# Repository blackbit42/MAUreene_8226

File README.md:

> [!WARNING]
> The current revision of the board is not functional. Build only if you want to work on fixing it.

# Token Ring MAU 'MAUreen'

MAUreene 8226 is a Token Ring (IEEE 802.5) Media Access Unit (MAU) that is inspired by the IBM 8226. For the most part, it is a reproduction of the IBM 8226, reduced to 2 'lobes', which is Token Ring lingo for what is known as a port in the context of other network technologies.

## Motivation

Token Ring is an interesting LAN technology. NICs are all over common auction sites and can be had cheaply, though MAUs are hard to come by. The intent of this project is to enable inclined people to play with Token Ring more easily.

## Clarification regarding 'crossover' cables

In an ethernet network you can nowadays connect two arbitrary devices with each other back to back without thinking about it, due to to the power of Auto MDI-X. Earlier you could use so-called 'crossover' cables. Unfortunately Token Ring doesn't support such a mode of interconnection, as a NIC goes through a mildly elaborated attachment process with a MAU. A mode where two hosts talk directly to each other doesn't exist, see [this](https://www.tavi.co.uk/ps2pages/ohland/8228.html#DirectCable).

## BOM analysis and mapping

| Original 8226 | Lobe 1 | Lobe 2  | Package      | Type                      | Measured value[^1] | Marking           | Remarks                             |
| ---           | ---    | ---     | ---          | ---                       | ---                | ---               | ---                                 |
| R2            | R1     | R21     | 0805         |                           | 4.8k               | 4871              |                                     |
| R10           | R2     | R22     | 0603         |                           | -None-             | -None-            | Opto-coupler biasing, not populated |
| R34           | R3     | R23     | 0603         |                           | 0.3                | 000               | RJ45 termination                    |
| R35           | R4     | R24     | 0603         |                           | 0.3                | 000               | RJ45 termination                    |
| R44           | R5     | R25     | 0603         |                           | 100                | 101               |                                     |
| R52           | R6     | R26     | 0603         |                           | 100                | 101               |                                     |
| R60           | R7     | R27     | 0603         |                           |                    | 104               |                                     |
| R68           | R8     | R28     | 0603         |                           | 10k                | 103               |                                     |
| R76           | R9     | R29     | 0603         |                           | 2k                 | 202               |                                     |
| R84           | R10    | R30     | 0805         |                           | 3.7k               | 3741              |                                     |
| R92           | R11    | R31     | 0603         |                           | 4.7k               | 472               | LED series resistor                 |
| R96           | R12    | R32     | 0603         |                           | 0.3                | 000               | RJ45 termination                    |
| R97           | R13    | R33     | 0603         |                           | 0.3                | 000               | RJ45 termination                    |
| C4            | C1     | C21     | 1812         | Ceramic                   | 330n               | -None-            |                                     |
| C12           | C2     | C22     | 1812         | Ceramic                   | 330n               | -None-            |                                     |
| C20           | C3     | C23     | EIA 7343-31  | Tantalum                  | 22u                | 22-20 LD (2)      |                                     |
| C34           | C4     | C24     | 0805         | Ceramic                   | 120n               | -None-            |                                     |
| C41           | C5     | C25     | 0805         | Ceramic                   | 120n               | -None-            |                                     |
| Q13           | Q1     | Q21     | SOT23        | BJT NPN                   |                    | 1P                |                                     |
| Q14           | Q2     | Q22     | SOT23        | BJT NPN                   |                    | 1P                |                                     |
| CR7           | D1     | D21     | SOT23        |                           | 0.6                | A66 (?)           | Flyback diode for coil in K2        |
| K2[^2]        | K1     | K21     | Non-standard | 4PDT                      |                    | P&B T84S17D214-12 |                                     |
| T2            | T1     | T21     | Non-standard | Special Token Ring        |                    | Valor PT4043      |                                     |
| DS2           | -None- | -None-  | Non-standard |                           |                    | -None-            | LEDs of J1A and J1B are used        |
| L2            | -None- | -None-  | -None-       | -None-                    |                    | -None-            | Unpopulated                         |
| U2            | U1     | U21     | DIP-6        | Opto-Coupler              |                    | QTC H11A1         |                                     | 
| -None-        | J1A    | J1B     | Non-standard | RJ45 jack                 |                    |                   |                                     |

## Power supply BOM

| Part designator | Value  | Description    |
| ---             | ---    | ---            |
| J200            |        | Barrel jack    |
| J201            |        | 2x2 jumper 12V |
| J202            |        | 2x2 jumper 5V  |
| U200            |        | 5V linear reg. |
| C200            | 0.33uF |                |
| C201            | 0.1uF  |                |
| C202            | 0.1uF  |                |
| R200            | 495Ohm | 12V rail ind.  |
| R201            | 145Ohm | 5V rail ind.   |

[^1]: Capacitors have been desoldered for measurement with HP 4262A LCR meter.
[^2]: The polarity of the coil supply is reversed, both in the original and this design. Irrelevant, as the relay coils do not have series diodes.

## Diode direction
CR7 is in a 3-pin SOT23 package, containing only a single diode. It is connected in parallel with a relay coil, indicating reverse EMF protection for adjacent devices in the circuit.
Unfortunately somebody got the direction wrong, hence there is significant reverse EMF with spikes of around 200V. 
Remarkably, neither the diode itself dies from excessive forward current when the relay is on, nor the switching transistor from the voltage spikes when the relay is being switched off.
In the design of this contraption, a diode with normal flyback operation has been foreseen.

## Pictures

Photo:

Kicad:

FreeCAD:

X-ray of original PCB, courtesy of [@Manawyrm](https://github.com/Manawyrm):

## Links

<https://www.ieee802.org/5/www8025org/>

<https://ardent-tool.com/network/Understanding_Token_Ring.html>

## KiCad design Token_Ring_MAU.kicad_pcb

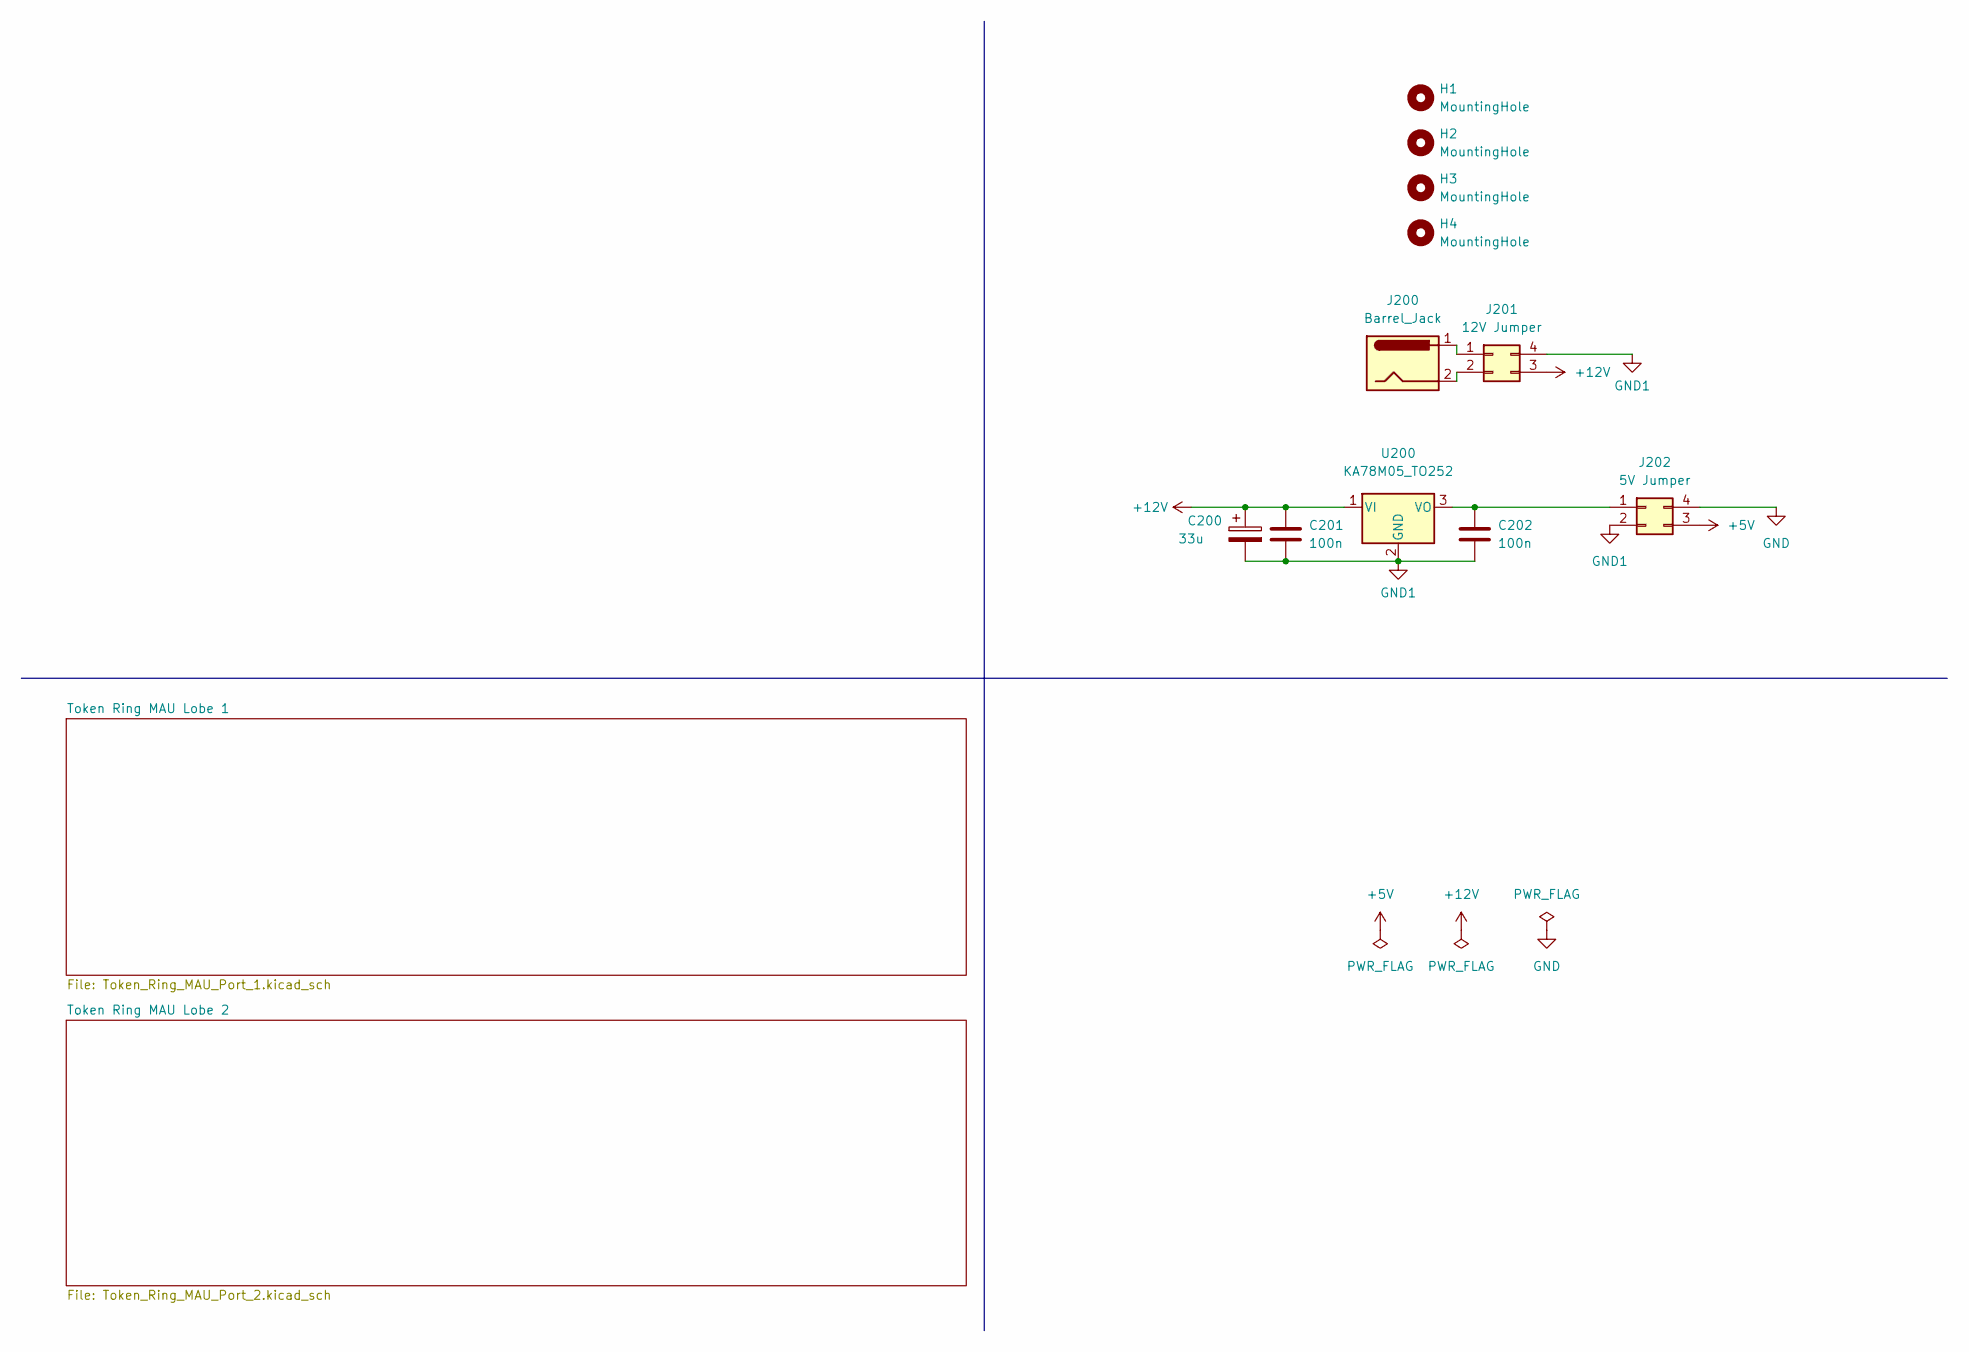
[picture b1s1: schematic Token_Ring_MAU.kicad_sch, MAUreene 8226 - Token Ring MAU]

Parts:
C200: 33u; CP_Elec_5x5.8; JLCPCB part number C128455
C201, C202: 100n; C_0805_2012Metric_Pad1.18x1.45mm_HandSolder; JLCPCB part number C85866
H1, H2, H3, H4: MountingHole; MountingHole_3.2mm_M3_DIN965_Pad; JLCPCB part number DNP
J200: Barrel_Jack; BarrelJack_CUI_PJ-063AH_Horizontal; JLCPCB part number DNP
J201: 12V Jumper; PinHeader_2x02_P2.54mm_Vertical; JLCPCB part number DNP
J202: 5V Jumper; PinHeader_2x02_P2.54mm_Vertical; JLCPCB part number DNP
U200: KA78M05_TO252; TO-252-2; JLCPCB part number DNP

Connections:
+5V: J202.3; also elsewhere on the board
+12V: C200.1, C201.1, J201.3, U200.1 (VI); also elsewhere on the board
GND: J202.4; also elsewhere on the board
GND1: C200.2, C201.2, C202.2, J201.4, J202.2, U200.2 (GND)
unnamed: C202.1, J202.1, U200.3 (VO)
unnamed: J200.1, J201.1
unnamed: J200.2, J201.2

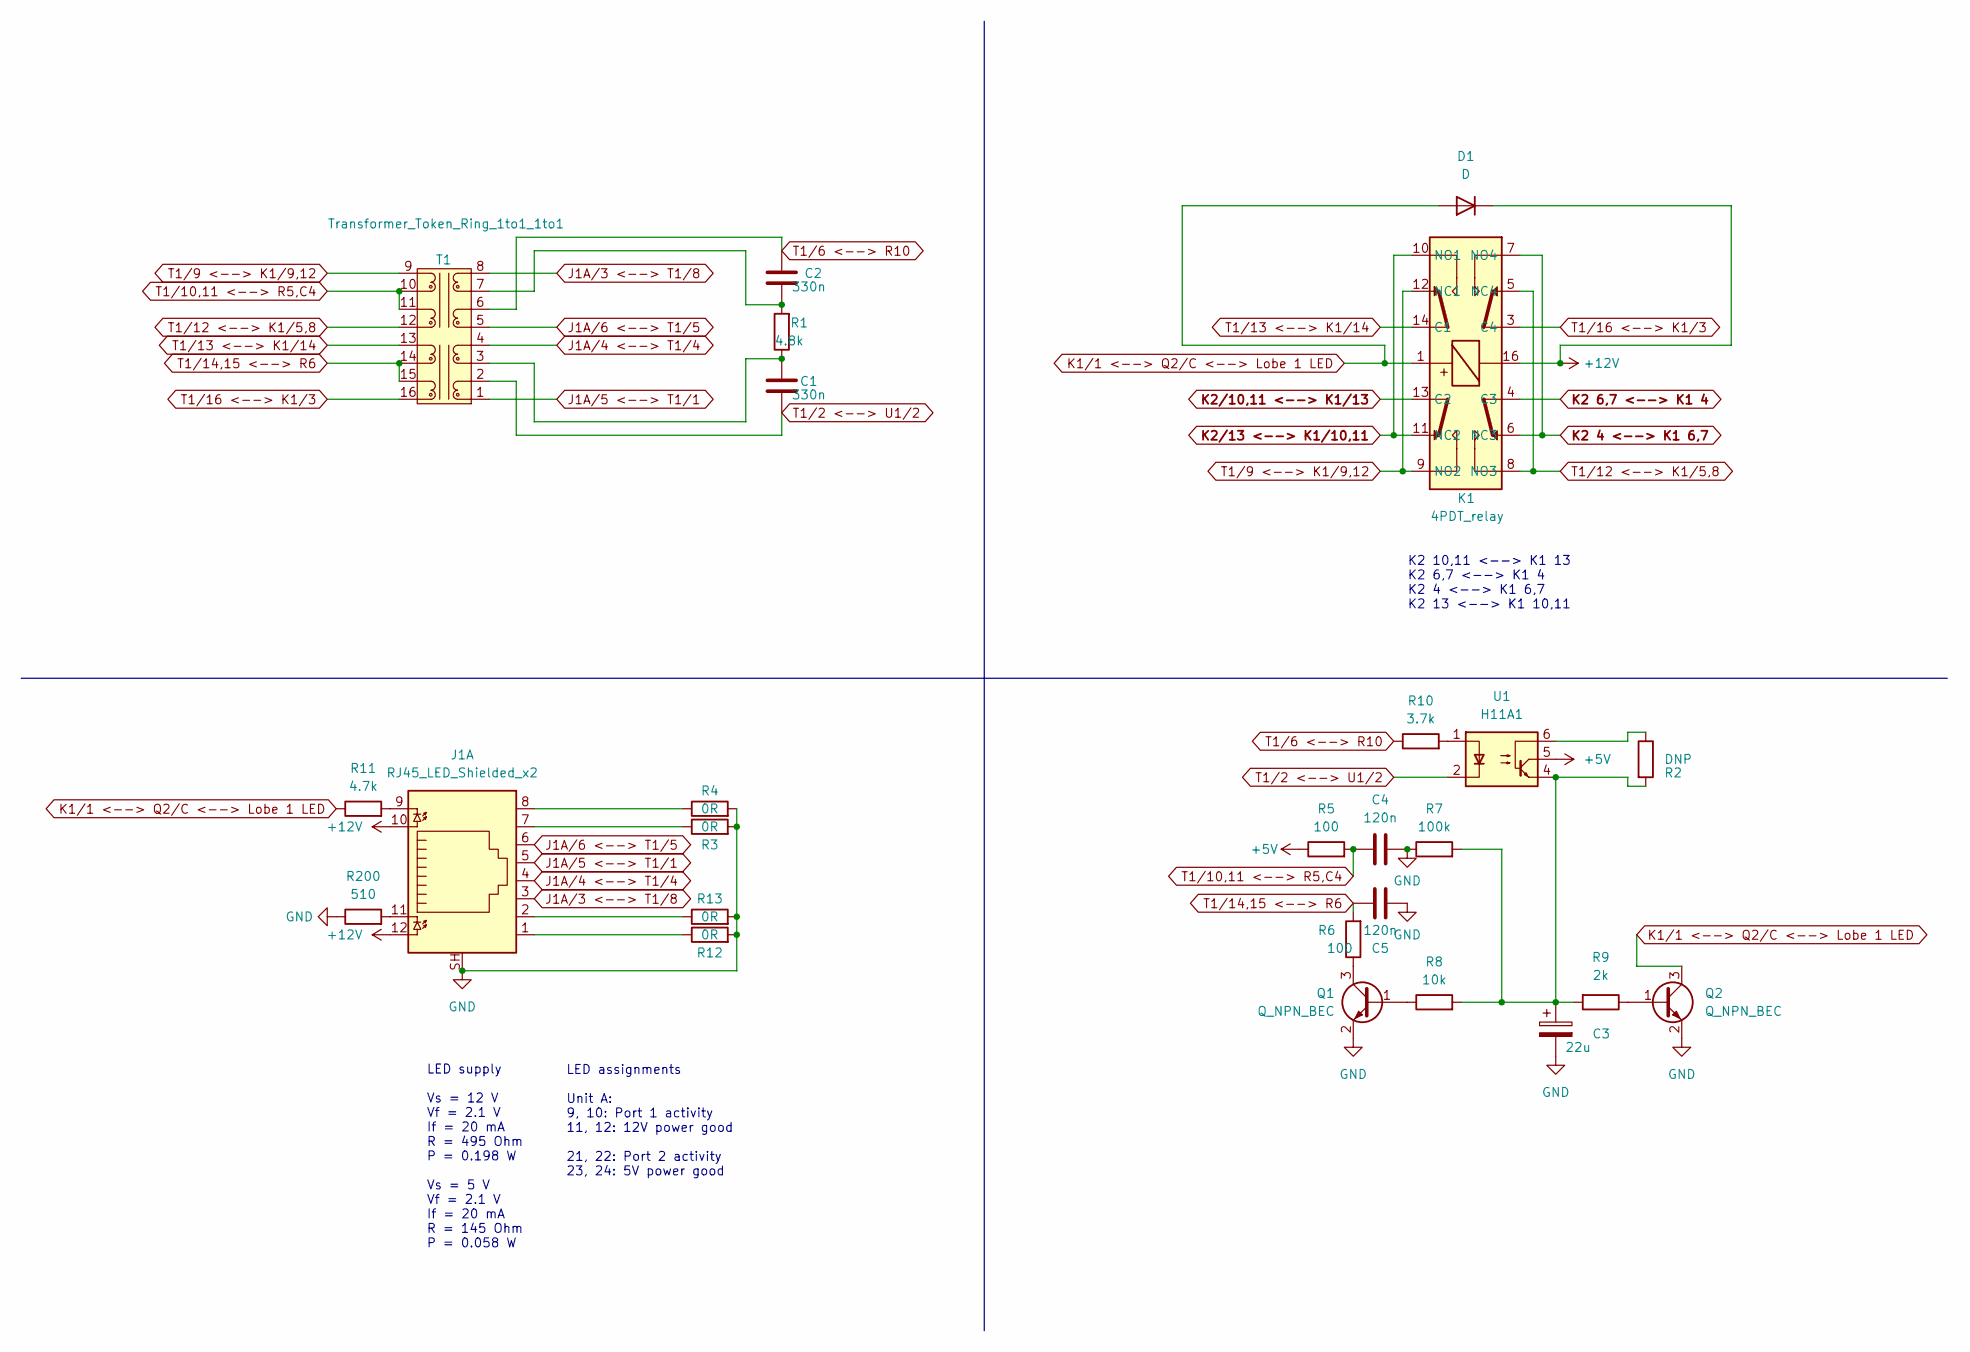
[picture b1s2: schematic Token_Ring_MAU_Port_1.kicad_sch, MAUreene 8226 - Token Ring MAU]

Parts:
C1, C2: 330n; C_1812_4532Metric_Pad1.57x3.40mm_HandSolder; JLCPCB part number C106167
C3: 22u; CP_EIA-7343-31_Kemet-D_Pad2.25x2.55mm_HandSolder; JLCPCB part number C7225
C4, C5: 120n; C_0603_1608Metric_Pad1.08x0.95mm_HandSolder; JLCPCB part number C282672
D1: D; D_SOD-123F; JLCPCB part number C108803
J1: RJ45_LED_Shielded_x2; RJ45_Amphenol_RJHSE538X-02; JLCPCB part number DNP
K1: 4PDT_relay; 4PDT_Relay; JLCPCB part number DNP
Q1, Q2: Q_NPN_BEC; SOT-23; JLCPCB part number C141788
R1: 4.8k; R_1206_3216Metric_Pad1.30x1.75mm_HandSolder; JLCPCB part number C323071
R2: DNP; R_1206_3216Metric_Pad1.30x1.75mm_HandSolder; JLCPCB part number DNP
R3, R4, R12, R13: 0R; R_0603_1608Metric_Pad0.98x0.95mm_HandSolder; JLCPCB part number C21189
R5, R6: 100; R_0603_1608Metric_Pad0.98x0.95mm_HandSolder; JLCPCB part number C445624
R7: 100k; R_0603_1608Metric_Pad0.98x0.95mm_HandSolder; JLCPCB part number C150003
R8: 10k; R_0603_1608Metric_Pad0.98x0.95mm_HandSolder; JLCPCB part number C100708
R9: 2k; R_0603_1608Metric_Pad0.98x0.95mm_HandSolder; JLCPCB part number C217936
R10: 3.7k; R_0805_2012Metric_Pad1.20x1.40mm_HandSolder; JLCPCB part number C403190
R11: 4.7k; R_0603_1608Metric_Pad0.98x0.95mm_HandSolder; JLCPCB part number C105428
R200: 510; R_0603_1608Metric_Pad0.98x0.95mm_HandSolder; JLCPCB part number C23193
T1: Transformer_Token_Ring_1to1_1to1; Pulse PE-64974; JLCPCB part number DNP
U1: H11A1; DIP-6_W7.62mm; JLCPCB part number DNP

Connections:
+5V: R5.1, U1.5; also elsewhere on the board
+12V: D1.1 (K), J1.10, J1.12, K1.16; also elsewhere on the board
GND: C3.2, C4.2, C5.2, J1.SH, Q1.2 (E), Q2.2 (E), R3.2, R4.2, R7.1, R12.2, R13.2, R200.1; also elsewhere on the board
J1A/3 <--> T1/8: J1.3, T1.8
J1A/4 <--> T1/4: J1.4, T1.4
J1A/5 <--> T1/1: J1.5, T1.1
J1A/6 <--> T1/5: J1.6, T1.5
K1/1 <--> Q2/C <--> Lobe 1 LED: D1.2 (A), K1.1, Q2.3 (C), R11.1
K2 4 <--> K1 6,7: K1.6 (NC3), K1.7 (NO4); also elsewhere on the board
K2 6,7 <--> K1 4: K1.4 (C3); also elsewhere on the board
K2/10,11 <--> K1/13: K1.13 (C2); also elsewhere on the board
K2/13 <--> K1/10,11: K1.10 (NO1), K1.11 (NC2); also elsewhere on the board
unnamed: C1.1, R1.1, T1.3
unnamed: C2.2, R1.2, T1.7
unnamed: C3.1, R2.2, R7.2, R8.2, R9.2, U1.4
unnamed: J1.1, R12.1
unnamed: J1.2, R13.1
unnamed: J1.7, R3.1
unnamed: J1.8, R4.1
unnamed: J1.9, R11.2
unnamed: J1.11, R200.2
unnamed: Q1.1 (B), R8.1
unnamed: Q1.3 (C), R6.1
unnamed: Q2.1 (B), R9.1
unnamed: R2.1, U1.6
unnamed: R10.2, U1.1
T1/2 <--> U1/2: C1.2, T1.2, U1.2
T1/6 <--> R10: C2.1, R10.1, T1.6
T1/9 <--> K1/9,12: K1.9 (NO2), K1.12 (NC1), T1.9
T1/10,11 <--> R5,C4: C4.1, R5.2, T1.10, T1.11
T1/12 <--> K1/5,8: K1.5 (NC4), K1.8 (NO3), T1.12
T1/13 <--> K1/14: K1.14 (C1), T1.13
T1/14,15 <--> R6: C5.1, R6.2, T1.14, T1.15
T1/16 <--> K1/3: K1.3 (C4), T1.16

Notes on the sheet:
K2 10,11 <--> K1 13 K2 6,7 <--> K1 4 K2 4 <--> K1 6,7 K2 13 <--> K1 10,11
LED assignments Unit A: 9, 10: Port 1 activity 11, 12: 12V power good 21, 22: Port 2 activity 23, 24: 5V power good
LED supply Vs = 12 V Vf = 2.1 V If = 20 mA R = 495 Ohm P = 0.198 W Vs = 5 V Vf = 2.1 V If = 20 mA R = 145 Ohm P = 0.058 W

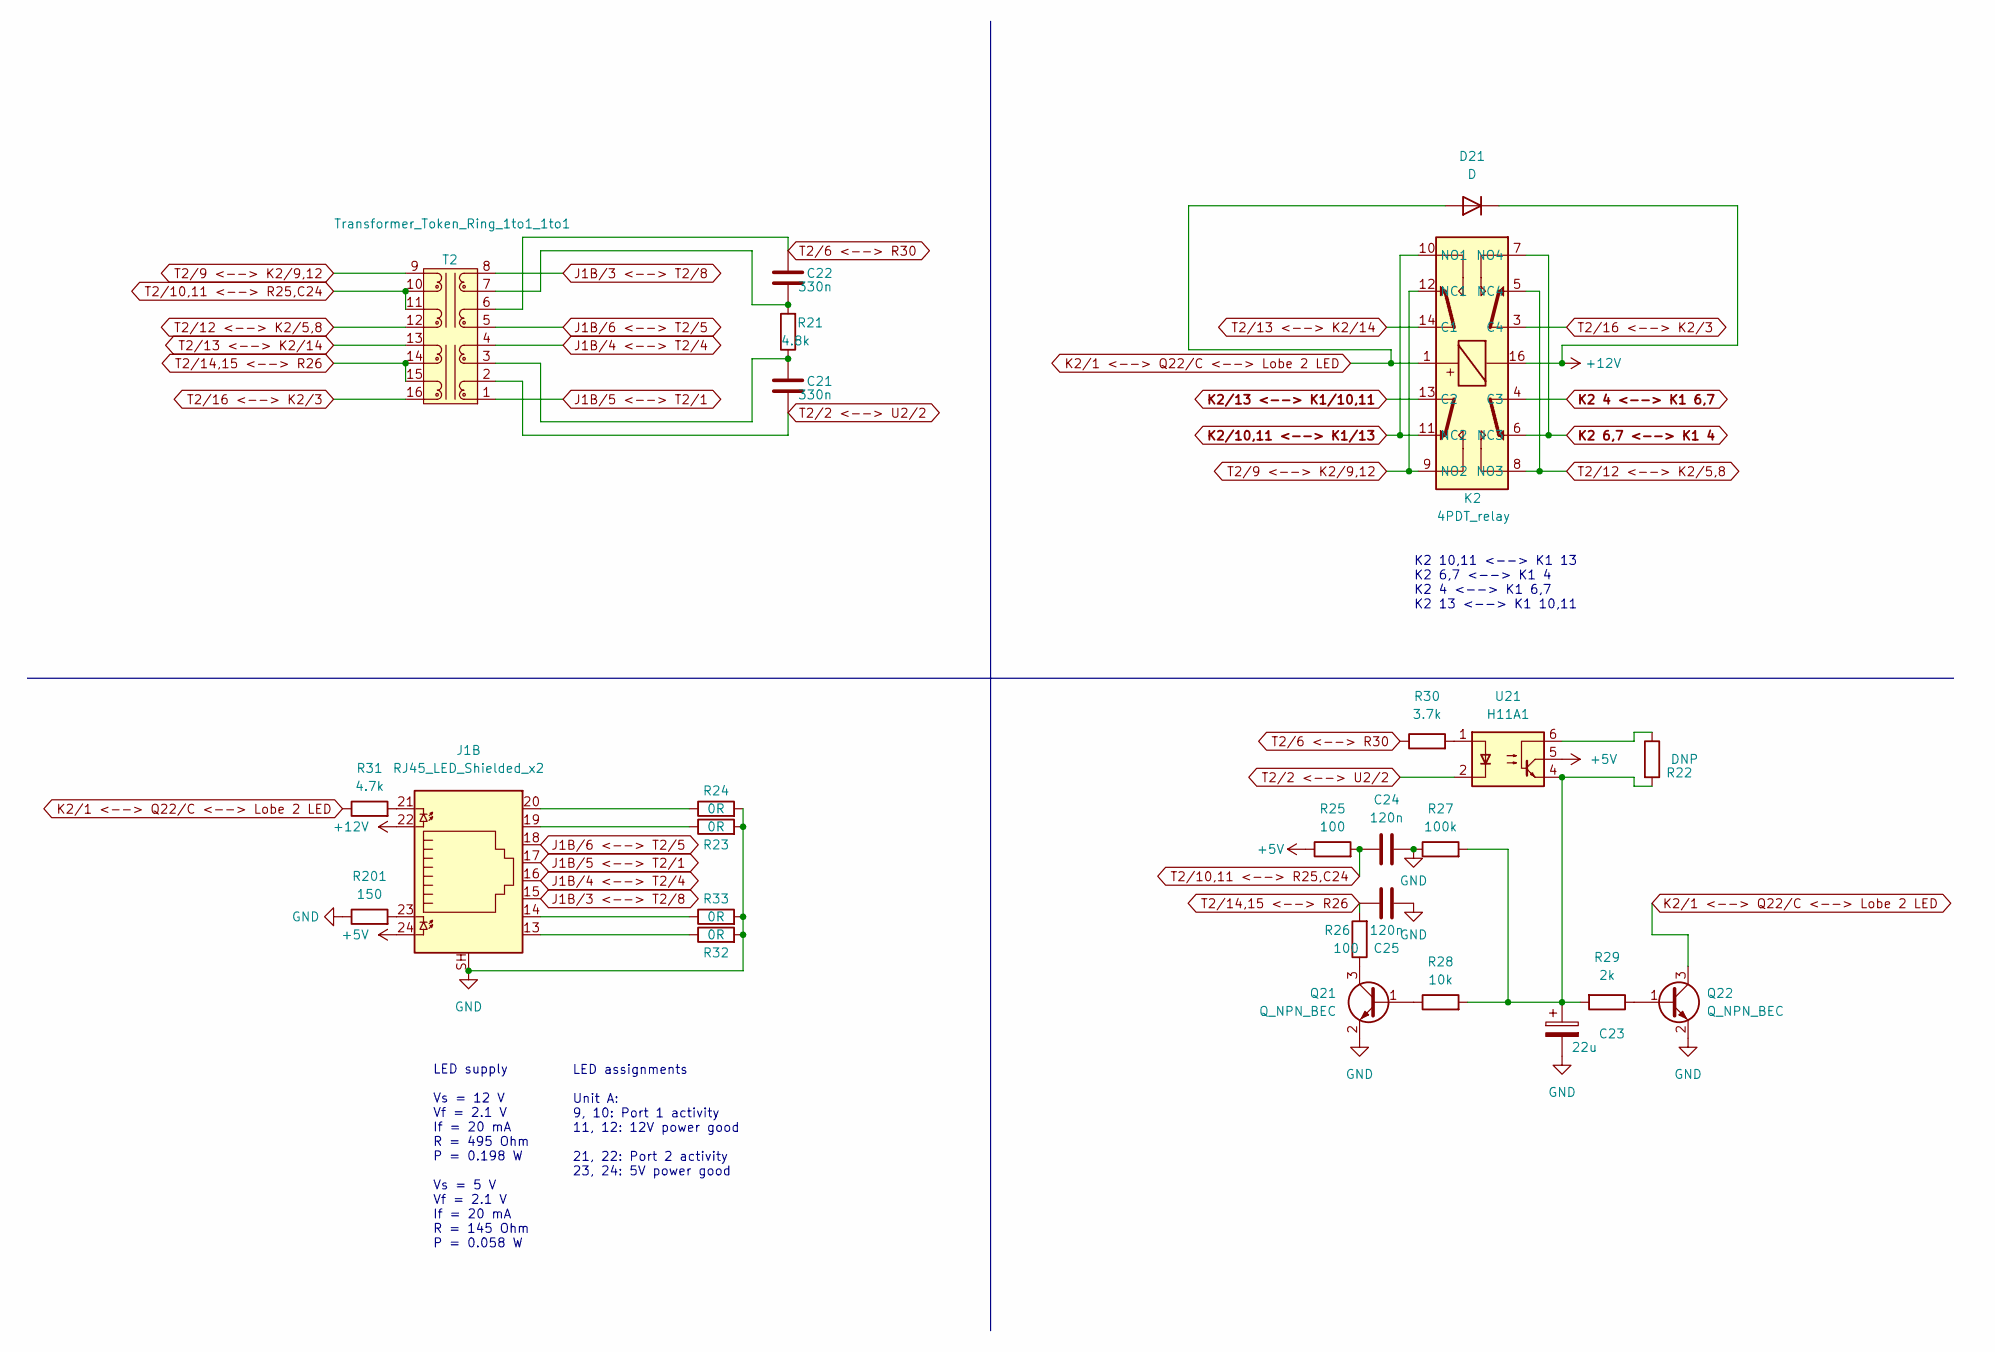
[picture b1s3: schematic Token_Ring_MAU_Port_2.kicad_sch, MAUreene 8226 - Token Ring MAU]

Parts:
C21, C22: 330n; C_1812_4532Metric_Pad1.57x3.40mm_HandSolder; JLCPCB part number C106167
C23: 22u; CP_EIA-7343-31_Kemet-D_Pad2.25x2.55mm_HandSolder; JLCPCB part number C7225
C24, C25: 120n; C_0603_1608Metric_Pad1.08x0.95mm_HandSolder; JLCPCB part number C282672
D21: D; D_SOD-123F; JLCPCB part number C108803
J1: RJ45_LED_Shielded_x2; RJ45_Amphenol_RJHSE538X-02; JLCPCB part number DNP
K2: 4PDT_relay; 4PDT_Relay; JLCPCB part number DNP
Q21, Q22: Q_NPN_BEC; SOT-23; JLCPCB part number C141788
R21: 4.8k; R_1206_3216Metric_Pad1.30x1.75mm_HandSolder; JLCPCB part number C323071
R22: DNP; R_1206_3216Metric_Pad1.30x1.75mm_HandSolder; JLCPCB part number DNP
R23, R24, R32, R33: 0R; R_0603_1608Metric_Pad0.98x0.95mm_HandSolder; JLCPCB part number C21189
R25, R26: 100; R_0603_1608Metric_Pad0.98x0.95mm_HandSolder; JLCPCB part number C445624
R27: 100k; R_0603_1608Metric_Pad0.98x0.95mm_HandSolder; JLCPCB part number C150003
R28: 10k; R_0603_1608Metric_Pad0.98x0.95mm_HandSolder; JLCPCB part number C100708
R29: 2k; R_0603_1608Metric_Pad0.98x0.95mm_HandSolder; JLCPCB part number C217936
R30: 3.7k; R_0805_2012Metric_Pad1.20x1.40mm_HandSolder; JLCPCB part number C403190
R31: 4.7k; R_0603_1608Metric_Pad0.98x0.95mm_HandSolder; JLCPCB part number C105428
R201: 150; R_0603_1608Metric_Pad0.98x0.95mm_HandSolder; JLCPCB part number C227596
T2: Transformer_Token_Ring_1to1_1to1; Pulse PE-64974; JLCPCB part number DNP
U21: H11A1; DIP-6_W7.62mm; JLCPCB part number DNP

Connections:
+5V: J1.24, R25.1, U21.5; also elsewhere on the board
+12V: D21.1 (K), J1.22, K2.16; also elsewhere on the board
GND: C23.2, C24.2, C25.2, J1.SH, Q21.2 (E), Q22.2 (E), R23.2, R24.2, R27.1, R32.2, R33.2, R201.1; also elsewhere on the board
J1B/3 <--> T2/8: J1.15, T2.8
J1B/4 <--> T2/4: J1.16, T2.4
J1B/5 <--> T2/1: J1.17, T2.1
J1B/6 <--> T2/5: J1.18, T2.5
K2 4 <--> K1 6,7: K2.4 (C3); also elsewhere on the board
K2 6,7 <--> K1 4: K2.6 (NC3), K2.7 (NO4); also elsewhere on the board
K2/1 <--> Q22/C <--> Lobe 2 LED: D21.2 (A), K2.1, Q22.3 (C), R31.1
K2/10,11 <--> K1/13: K2.10 (NO1), K2.11 (NC2); also elsewhere on the board
K2/13 <--> K1/10,11: K2.13 (C2); also elsewhere on the board
unnamed: C21.1, R21.1, T2.3
unnamed: C22.2, R21.2, T2.7
unnamed: C23.1, R22.2, R27.2, R28.2, R29.2, U21.4
unnamed: J1.13, R32.1
unnamed: J1.14, R33.1
unnamed: J1.19, R23.1
unnamed: J1.20, R24.1
unnamed: J1.21, R31.2
unnamed: J1.23, R201.2
unnamed: Q21.1 (B), R28.1
unnamed: Q21.3 (C), R26.1
unnamed: Q22.1 (B), R29.1
unnamed: R22.1, U21.6
unnamed: R30.2, U21.1
T2/2 <--> U2/2: C21.2, T2.2, U21.2
T2/6 <--> R30: C22.1, R30.1, T2.6
T2/9 <--> K2/9,12: K2.9 (NO2), K2.12 (NC1), T2.9
T2/10,11 <--> R25,C24: C24.1, R25.2, T2.10, T2.11
T2/12 <--> K2/5,8: K2.5 (NC4), K2.8 (NO3), T2.12
T2/13 <--> K2/14: K2.14 (C1), T2.13
T2/14,15 <--> R26: C25.1, R26.2, T2.14, T2.15
T2/16 <--> K2/3: K2.3 (C4), T2.16

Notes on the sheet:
LED supply Vs = 12 V Vf = 2.1 V If = 20 mA R = 495 Ohm P = 0.198 W Vs = 5 V Vf = 2.1 V If = 20 mA R = 145 Ohm P = 0.058 W
LED assignments Unit A: 9, 10: Port 1 activity 11, 12: 12V power good 21, 22: Port 2 activity 23, 24: 5V power good
K2 10,11 <--> K1 13 K2 6,7 <--> K1 4 K2 4 <--> K1 6,7 K2 13 <--> K1 10,11

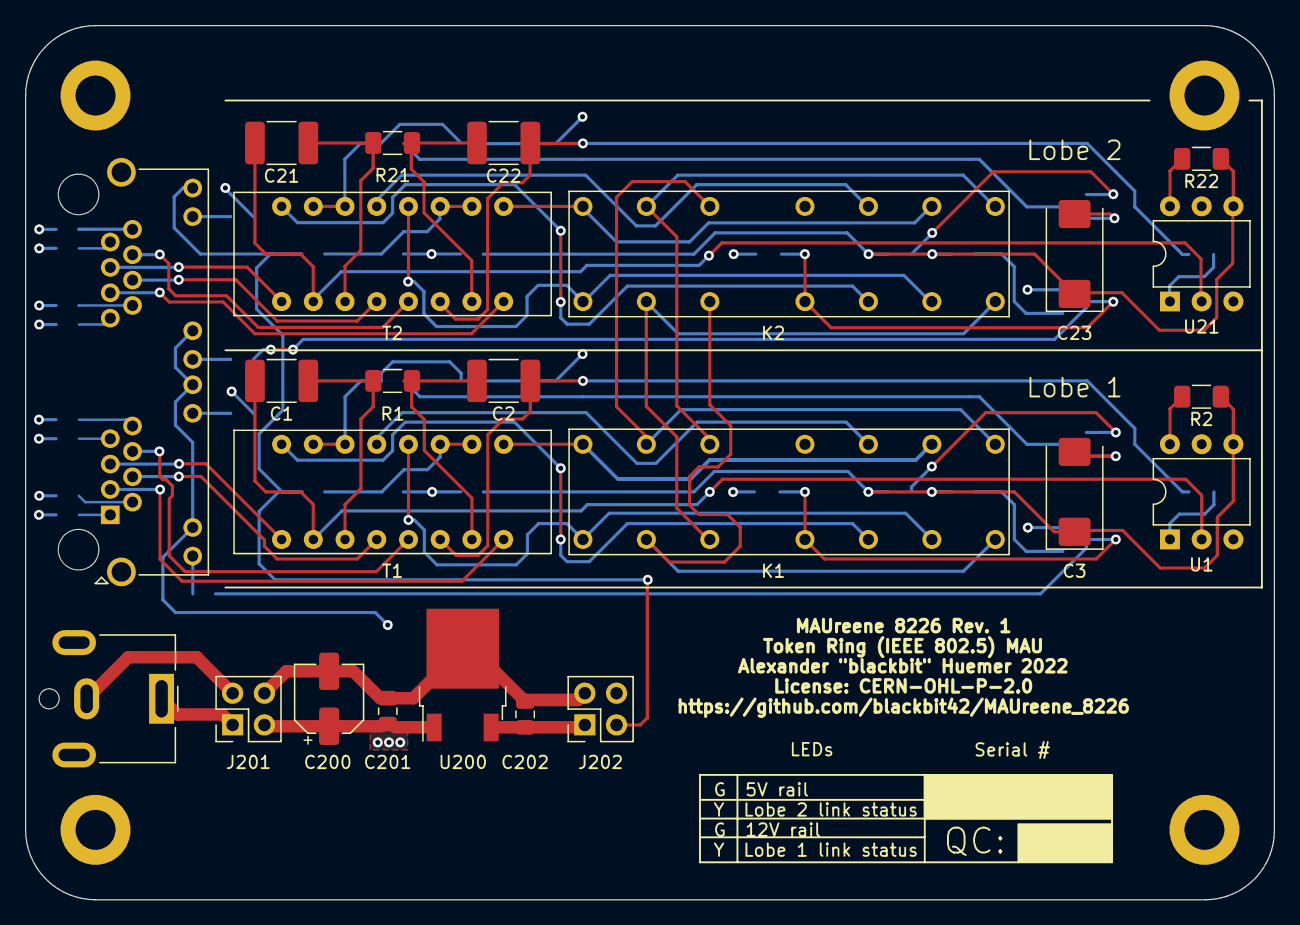
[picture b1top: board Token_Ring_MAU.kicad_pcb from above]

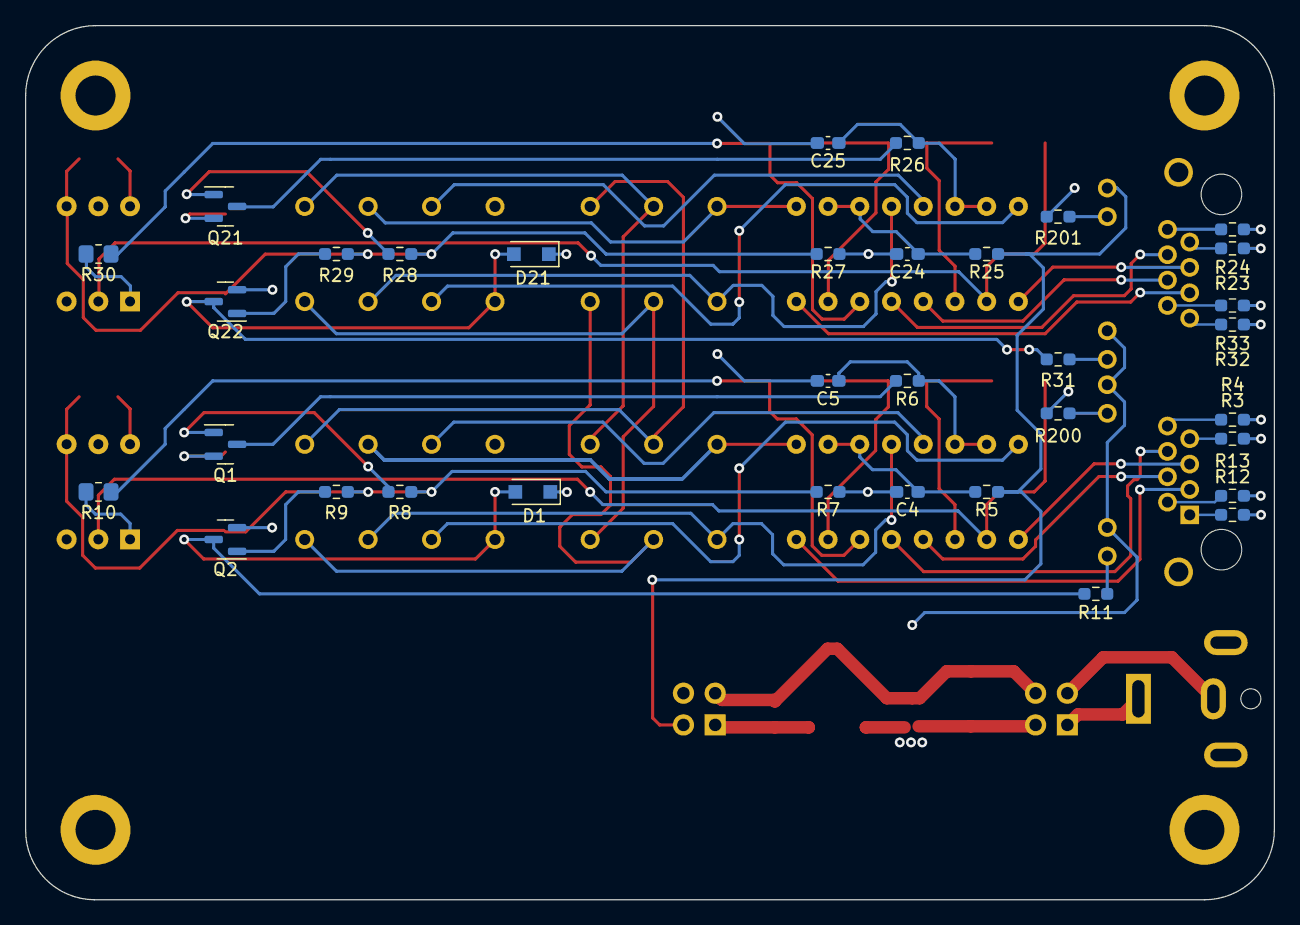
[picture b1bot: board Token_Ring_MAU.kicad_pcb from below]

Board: 4 copper layers, 100.0 x 70.0 mm, 62 parts (34 on the bottom side), 65 nets.

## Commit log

2022-12-03 root-commit
2023-09-08 Add pictures, gerbers, warning note

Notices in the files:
Token_Ring_MAU.kicad_pcb:
License: CERN-OHL-P-2.0
